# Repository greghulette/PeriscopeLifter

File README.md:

# PeriscopeLifter
Files and Basic Instructions for my Periscope Lifter

Latest version is V0.4

The latest instructions can be found here: https://docs.google.com/document/d/1gkrul7UIyUIZ05SwGsmy0yHRKMRutKzC-wxl7RRob7I/edit?usp=sharing

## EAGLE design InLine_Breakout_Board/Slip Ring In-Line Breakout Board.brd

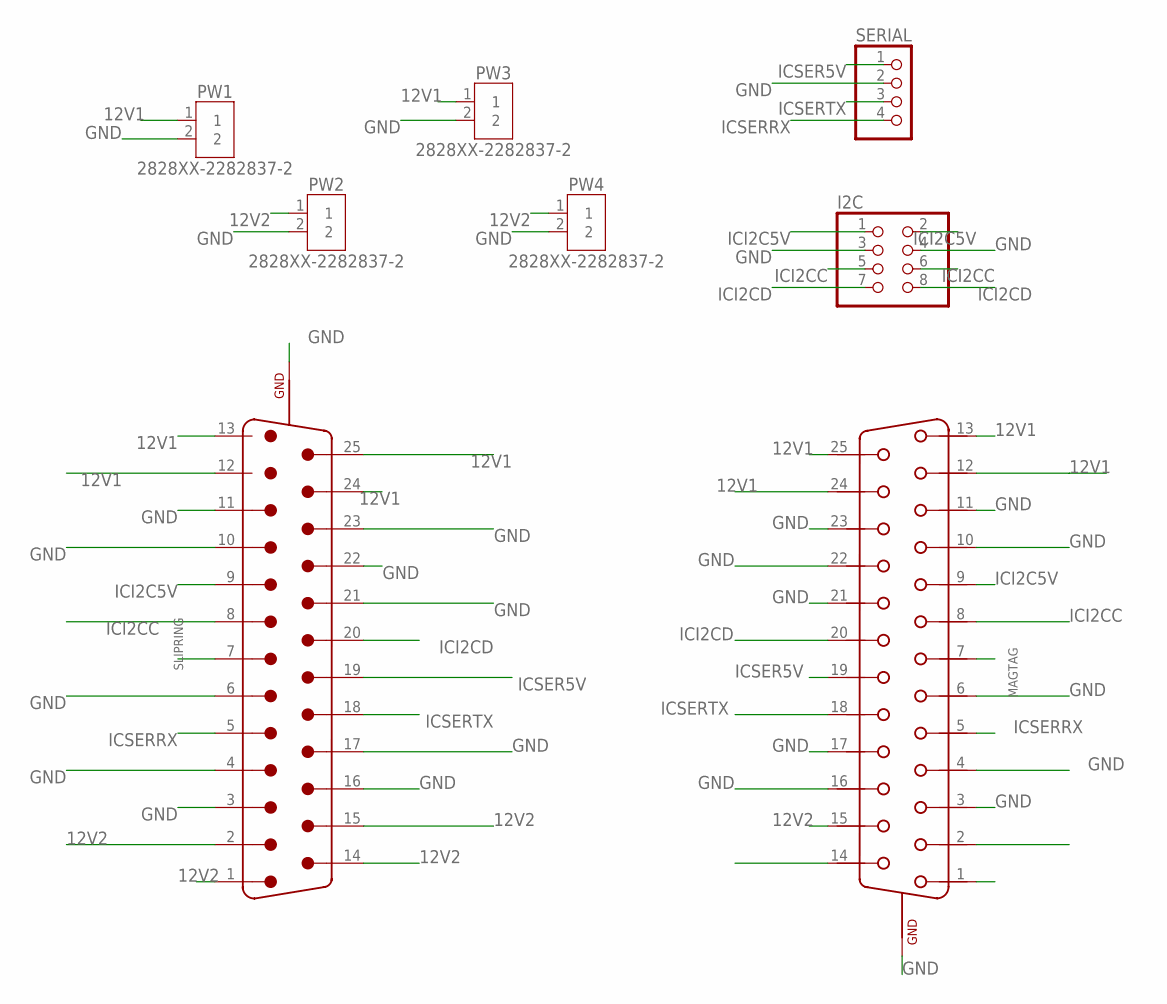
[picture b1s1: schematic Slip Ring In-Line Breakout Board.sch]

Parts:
I2C: PINHD-2X4; 2X04; MPN 2213S-08G
MAGTAG: WE-D-SUB_THT_UNC4/40_214611023; MPN 61802525123
PW1, PW2, PW3, PW4: 2828XX-2282837-2; TERMBLK_508-2N; MPN 20020316-H021B01LF
SERIAL: PINHD-1X4; 1X04; MPN 22-28-4041
SLIPRING: WE-D-SUB_THT_UNC4/40_214111023; MPN 61802525023

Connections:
12V1: MAGTAG.12 (2), MAGTAG.13 (1), MAGTAG.24 (15), MAGTAG.25 (14), PW1.1, PW3.1, SLIPRING.12, SLIPRING.13, SLIPRING.24, SLIPRING.25
12V2: MAGTAG.14 (25), MAGTAG.15 (24), PW2.1, PW4.1, SLIPRING.1, SLIPRING.2, SLIPRING.14, SLIPRING.15
GND: I2C.3, I2C.4, MAGTAG.3 (11), MAGTAG.4 (10), MAGTAG.6 (8), MAGTAG.10 (4), MAGTAG.11 (3), MAGTAG.16 (23), MAGTAG.17 (22), MAGTAG.21 (18), MAGTAG.22 (17), MAGTAG.23 (16), MAGTAG.Z1 (GND), MAGTAG.Z2 (GND), PW1.2, PW2.2, PW3.2, PW4.2, SERIAL.2, SLIPRING.3, SLIPRING.4, SLIPRING.6, SLIPRING.10, SLIPRING.11, SLIPRING.16, SLIPRING.17, SLIPRING.21, SLIPRING.22, SLIPRING.23, SLIPRING.Z1 (GND), SLIPRING.Z2 (GND)
ICI2C5V: I2C.1, I2C.2, MAGTAG.9 (5), SLIPRING.9
ICI2CC: I2C.5, I2C.6, MAGTAG.8 (6), SLIPRING.8
ICI2CD: I2C.7, I2C.8, MAGTAG.20 (19), SLIPRING.20
ICSER5V: MAGTAG.19 (20), SERIAL.1, SLIPRING.19
ICSERRX: MAGTAG.5 (9), SERIAL.4, SLIPRING.5
ICSERTX: MAGTAG.18 (21), SERIAL.3, SLIPRING.18

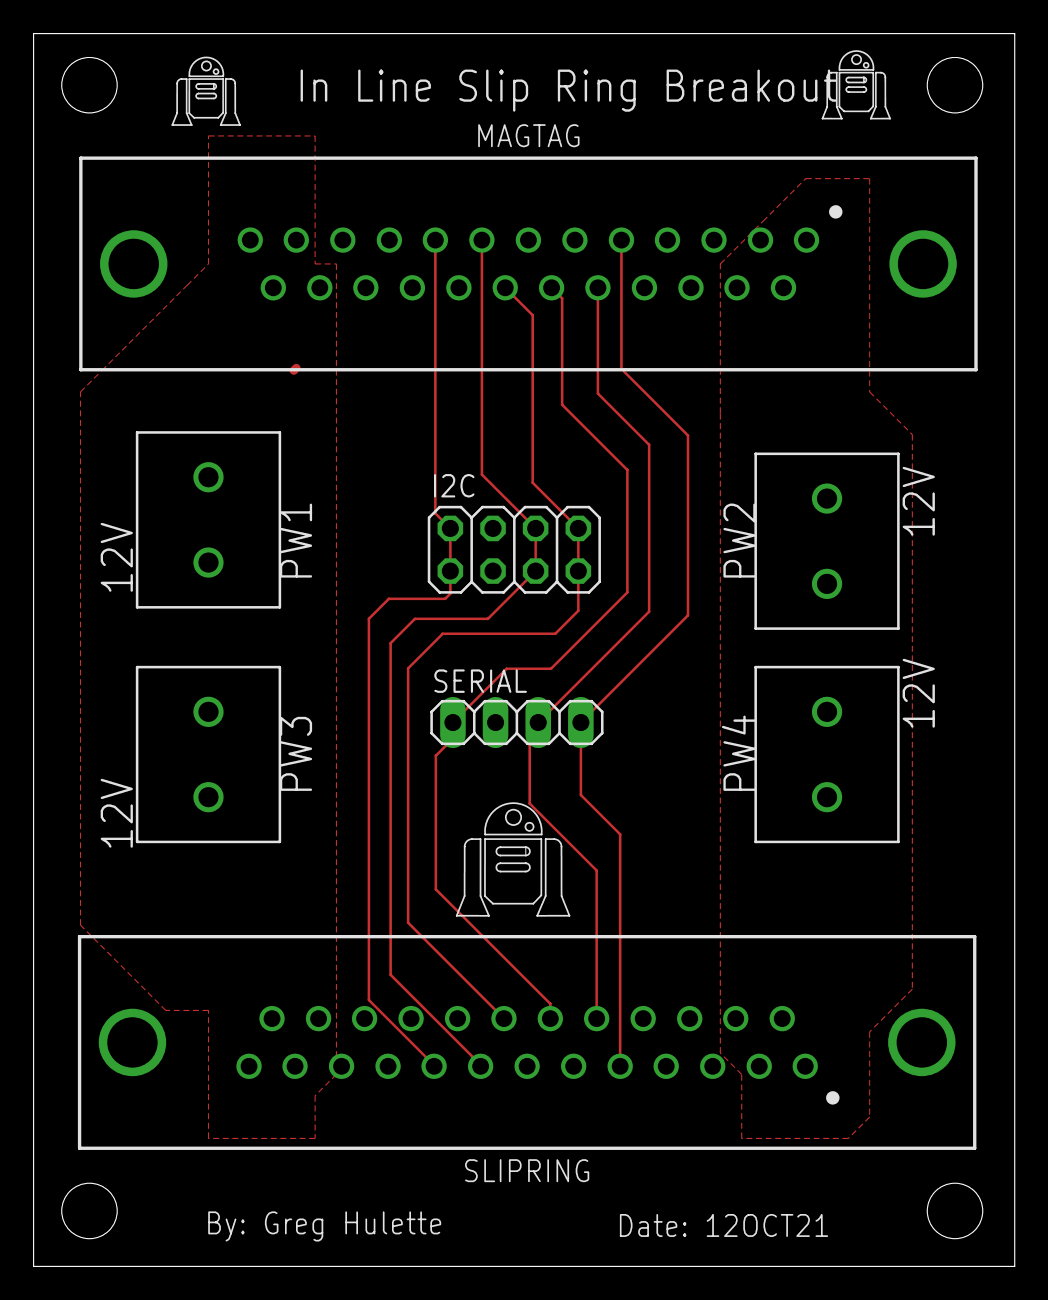
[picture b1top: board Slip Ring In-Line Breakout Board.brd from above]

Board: 2 copper layers, 58.4 x 73.4 mm, 8 parts (0 on the bottom side), 9 nets.

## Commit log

2021-09-28 Something:
2021-09-29 uploaded the baseplate file
2021-10-15 Added files and instructions
2021-10-21 Archive
    Archived some files
2021-11-07 Added In-Line Slip Ring Breakout Board
2022-02-28 Added the Fusion 360 Files
2022-03-01 Individual Exports from Fusion 360
2022-03-02 Organized and updated files in the V0.3 Folder
2022-03-03 Updated Files and created STLs
2022-03-03 Added drill guides
2022-03-04 Updated the Nut Lock File and Added the Full Assembly
2022-03-04 Updated the Main Assembly File and adjust others
2022-03-14 Updated some files.
2022-03-25 Added the Electronics Rotary Mount
2022-03-30 Updated the Spacer for the Uppity Spinner
2022-04-04 Updated the Rotary Motor Mount
2022-04-04 Little Update to Rotary Mount
2022-04-06 Uploaded the PCB's for the Rotary and modified Lifter for the Uppity Spinner.
2022-04-06 Removed OS generated files
2022-04-06 Added step files for V 0.3
2022-06-07 Added a version to test with a larger OD/ID pipe
2022-06-13 Made a V2 folder for the larger pipe tests
2022-06-28 Nothing to see here.
2022-07-05 Updates to the larger pipe tests
2023-01-09 Created a V 0.4
2023-01-09 Updated the Read mes
2023-03-08 Removed some files in V0.4

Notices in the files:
parts and their libraries:
Wurth_Signal: Copyright: Würth Elektronik
